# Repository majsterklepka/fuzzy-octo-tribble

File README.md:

# Electrical equipments
diy ac 3-pin socket tester

Hi, Jak się macie?

Zaprezentuje Wam dziś projekt testera gniazd sieciowych 230-240V. Projekt zaczerpnięty z [instructables.com](https://www.instructables.com/id/DIY-AC-3-Pin-Socket-Tester/ "Instructables.com").

Z uwagi na fakt, że projekt dotyczy kontaktu z siecią prądu przemiennego 230V(Europa), wykonanie go wymaga ogromnego doświadczenia i pewnej, dość dużej wprawy w pracach z napięciem sieciowym.

Do wykonania, potrzeba:
- trzy rezystory 2W, 47k
- trzy diody LED,
- trzy zwykłe diody prostownicze, o napięciu wstecznym min. 1000V i prądzie min. 1A
- płytka drukowana według dokumentacji zawartej w katalogu [KiCad](/KiCad "Dokumentacja")
- obudowa, wykonana na drukarce 3D, [obudowa STL](/3dhousing "3Dhousing")
- mocowania kabla testowego, [Dokumentacja -> blaszka, obudowa](/mechanical "mechanical")
- kabel sieciowy, zalewany, trzy-żyłowy, z wtyczką, z uziemieniem

## Krótka instrukcja obsługi

| LED1 |LED2 | LED3 | opis |
| :---: | :---: | :---: | :--- | 
| X | X | | wszystko OK |
| X | | | niepodłączona ziemia(E) |
| | X | X | sieć(L) - ziemia(E) odwrócone |
| X | | X | sieć(L) - zero(N) odwrócone |
| | X | | brak zero(N) |
| | | | brak sieci(L)/brak zero(N) i brak ziemi(E) | 

## Credits

Jak zwykle i ten projekt jest dostępny na zasadach Wolnych Licencji:
- [CC-BY-SA 4.0](https://creativecommons.org/licenses/by-sa/4.0/ "license")

>:warning:**Uwaga!!!**  
>
>W układzie występuje niebezpieczne dla życia napięcie sieciowe!  
>Po montażu, płytkę drukowaną należy zaizolować lakierem poliuretanowym!  
>a elementy obudowy, wieko z puszką obudowy skleić!  
>przepust należy wypełnić silikonem!  

- - - 

Baw się dobrze, czuj się wolny i pamiętaj o Autorze(ach)! Podziel się tym projektem ze swoimi przyjaciółmi.

_Msc. Paweł Sobótka (SQ7EQE)_

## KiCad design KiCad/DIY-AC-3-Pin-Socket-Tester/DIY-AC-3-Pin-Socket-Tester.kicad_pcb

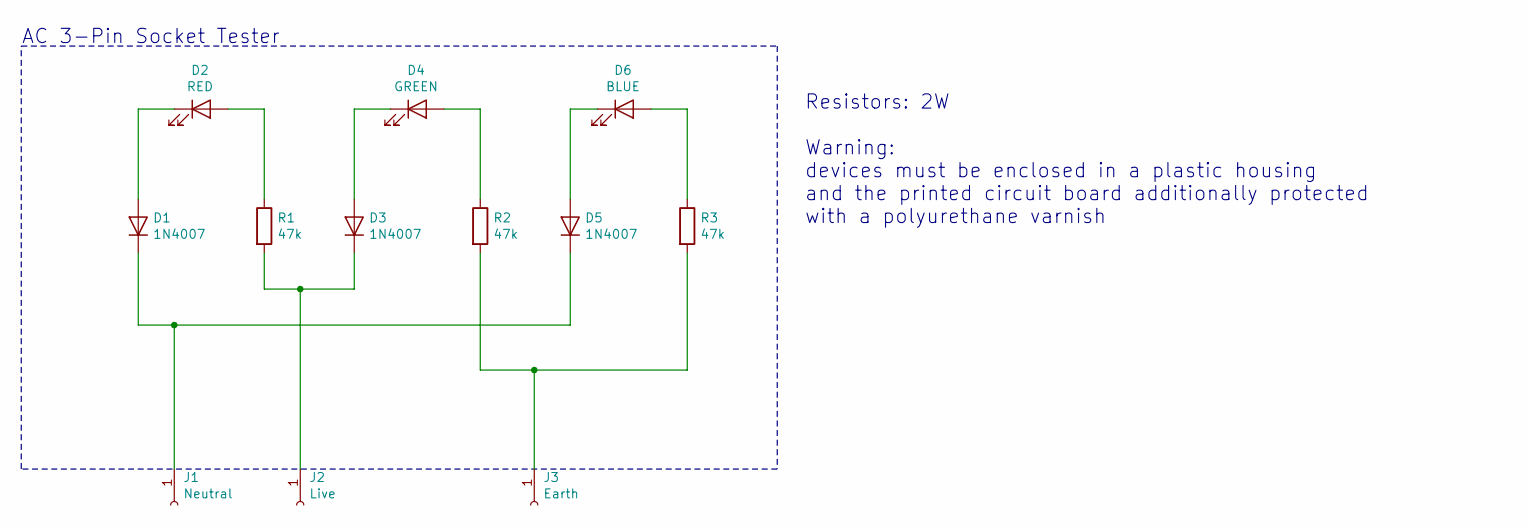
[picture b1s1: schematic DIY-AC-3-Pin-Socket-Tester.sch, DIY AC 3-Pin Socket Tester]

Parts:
D1, D3, D5: 1N4007; D_DO-41_SOD81_P10.16mm_Horizontal
D2: RED; LED_D5.0mm
D4: GREEN; LED_D5.0mm
D6: BLUE; LED_D5.0mm
J1: Neutral; Pin_D1.0mm_L10.0mm
J2: Live; Pin_D1.0mm_L10.0mm
J3: Earth; Pin_D1.0mm_L10.0mm
R1, R2, R3: 47k; R_Axial_DIN0414_L11.9mm_D4.5mm_P15.24mm_Horizontal

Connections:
unnamed: D1.1 (K), D5.1 (K), J1.1
unnamed: D1.2 (A), D2.1 (K)
unnamed: D2.2 (A), R1.1
unnamed: D3.1 (K), J2.1, R1.2
unnamed: D3.2 (A), D4.1 (K)
unnamed: D4.2 (A), R2.1
unnamed: D5.2 (A), D6.1 (K)
unnamed: D6.2 (A), R3.1
unnamed: J3.1, R2.2, R3.2

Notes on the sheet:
Resistors: 2W Warning: devices must be enclosed in a plastic housing and the printed circuit board additionally protected with a polyurethane varnish
AC 3-Pin Socket Tester

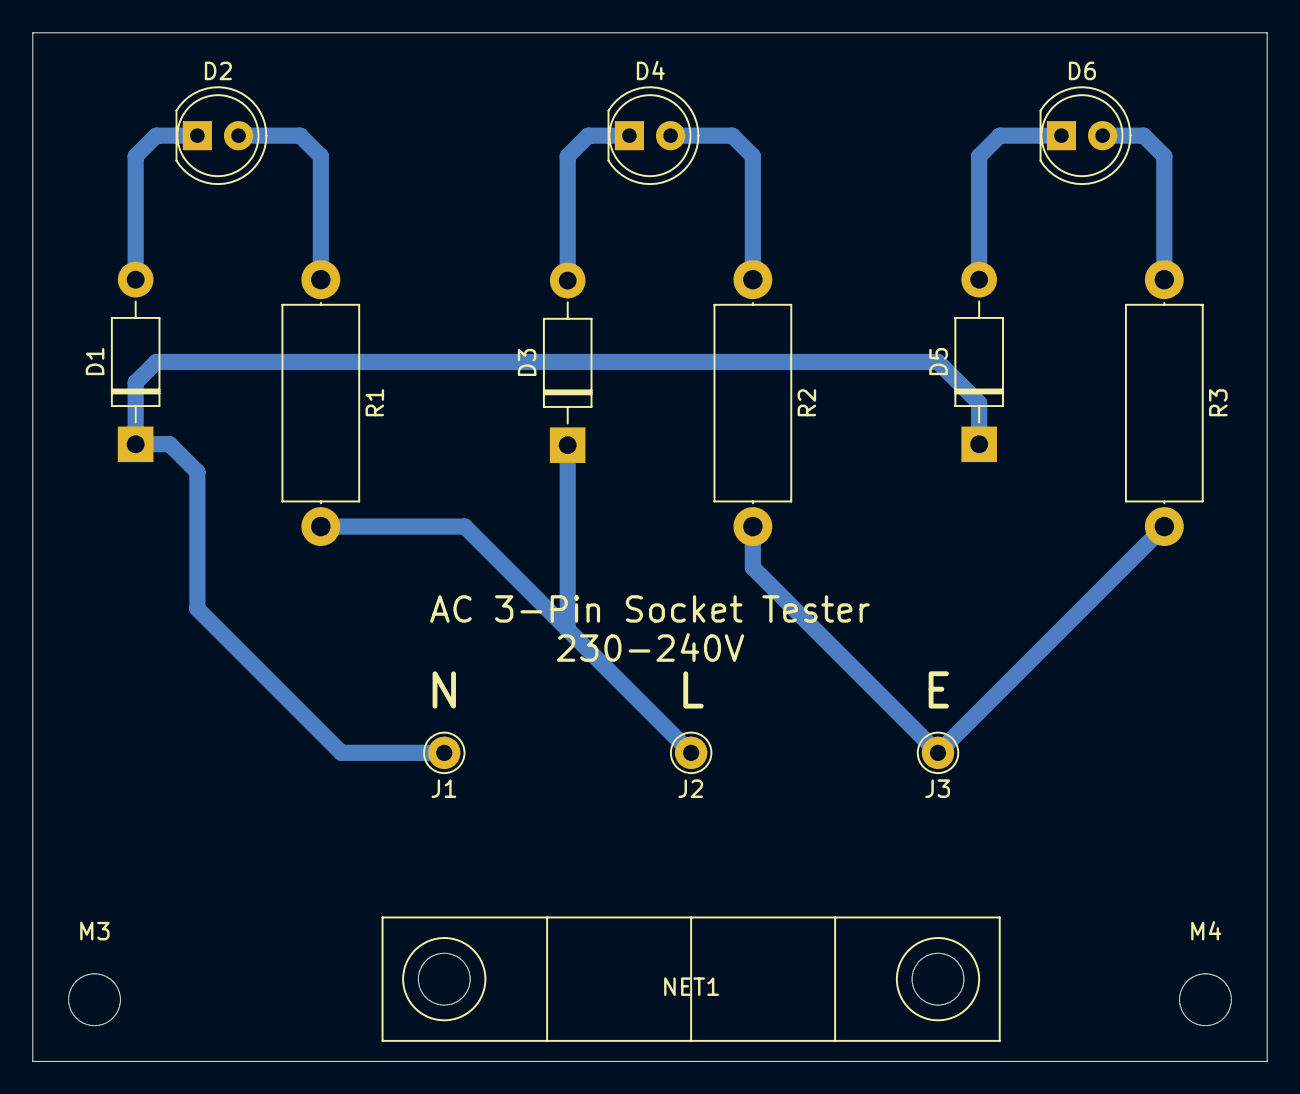
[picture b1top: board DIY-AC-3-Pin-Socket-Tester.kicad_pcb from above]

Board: 2 copper layers, 76.2 x 63.5 mm, 15 parts (0 on the bottom side), 9 nets.

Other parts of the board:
M3, M4: MountingHole_3.2mm_M3
NET1: net-cable-conn

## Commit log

2020-05-04 new project file
2020-05-04 update file
2020-05-05 add emoji
